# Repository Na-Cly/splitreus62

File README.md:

# splitreus62

Spacing on this is for choc keycaps only. MX sized keycaps will not work.

- [Atreus](https://github.com/technomancy/atreus) Phil Hagelberg
- [Atreus62](https://github.com/profet23/atreus62) Profet23

All these files were created from scratch, but out of respect for Phil I wanted to GPLv3 the project. 

Thanks to Phil for the staggering measurements from the atreus, and profet23 for the 62 key variant. 

This project uses MIT licensed KiCad footprints from Keebio and the Lily58 project.

### Features: 
- Reversible PCB supports MX/Alps/Choc Modified from keebio footprint.
- Pro Micro Footprint borrowed from the Lily58.
- supports SMD and through hole diodes.
- Breakout pins for led underglow.

### Known issues:
- SMD Diode footprint is only on the back-copper layer, so diodes have to be mounted on the bottom of the left half and the top of the right half.

## [Build Guide](/guide/README.MD)

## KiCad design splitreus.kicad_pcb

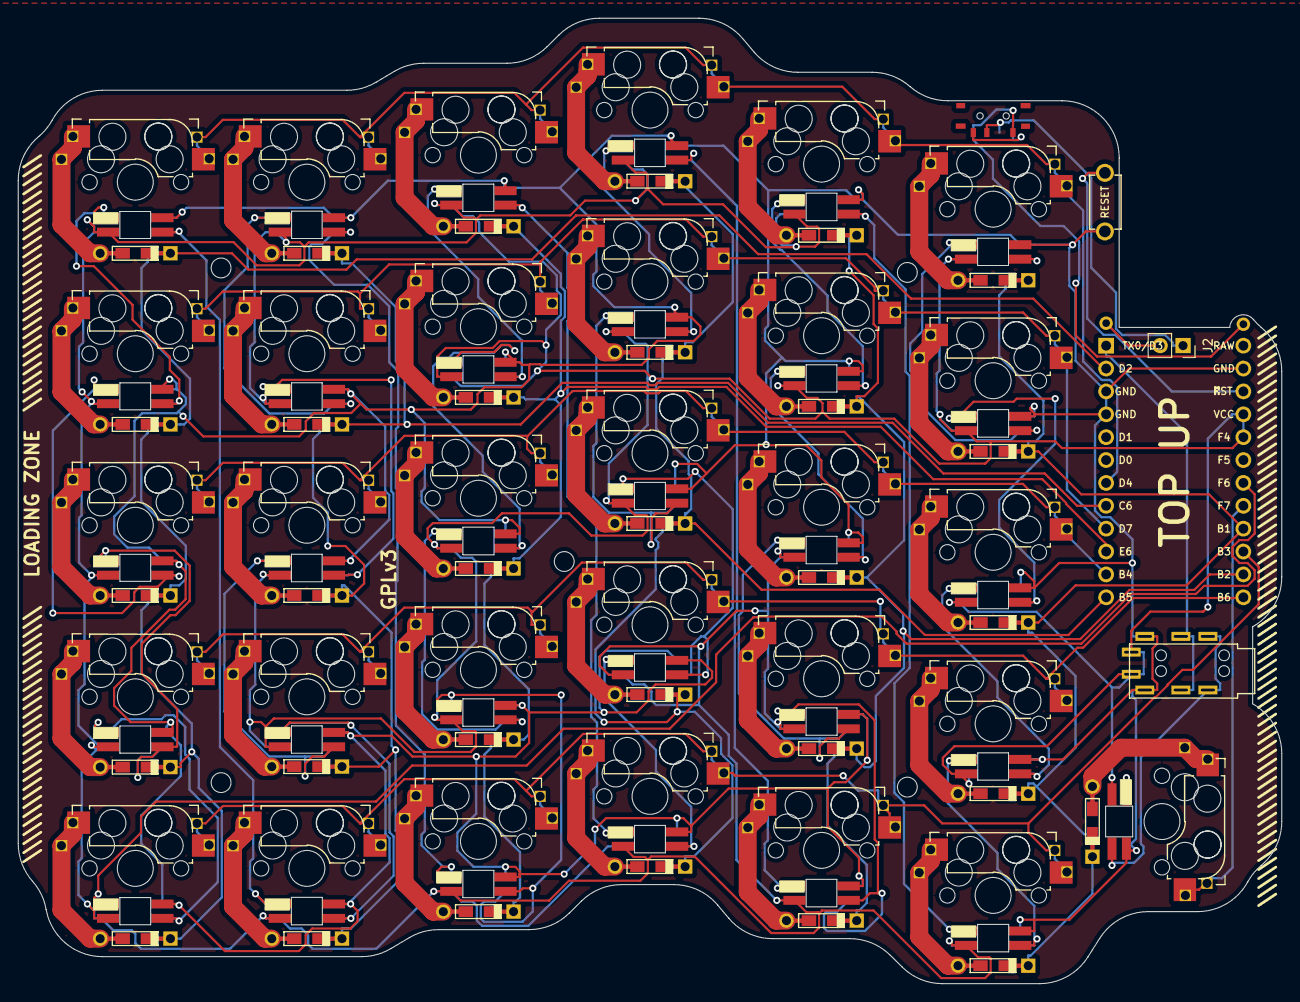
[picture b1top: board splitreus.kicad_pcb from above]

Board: 2 copper layers, 140.3 x 107.2 mm, 103 parts (1 on the bottom side), 81 nets.

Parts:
D0, D1, D2, D3, D4, D5, D6, D7, D8, D9, D10, D11, D12, D13, D14, D15, D16, D17, D18, D19, D20, D21, D22, D23, D24, D25, D26, D27, D28, D29, D30: 1N4148; Diode-Hybrid-reversible
D90, D91, D92, D93, D94, D95, D96, D97, D98, D99, D910, D911, D912, D913, D914, D915, D916, D917, D918, D919, D920, D921, D922, D923, D924, D925, D926, D927, D928, D929, D930: SK6812MINI; sk6812_minie_reversible
J1: TRRS; MJ-4PP-9
J2: battery; PinSocket_1x02_P2.54mm_Vertical
RST1: RST_SWITCH; TACT_SWITCH_TVBP06
SW0, SW1, SW2, SW3, SW4, SW5, SW6, SW7, SW8, SW9, SW10, SW11, SW12, SW13, SW14, SW15, SW16, SW17, SW18, SW19, SW20, SW21, SW22, SW23, SW24, SW25, SW26, SW27, SW28, SW29, SW30: SW_PUSH; Kailh_socket_MX_reversible_fix
SW91: SW_SPDT; reversible_power
U0: ProMicro; nice_nano
U1, U2, U3, U4, U5: HOLE; MountingHole_2.2mm_M2_DIN965

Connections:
B+: J2.1, SW91.2
B-: J2.2, U0.B-
COL0: D0.2, D1.2, D2.2, D3.2, D4.2, U0.2
COL1: D5.2, D6.2, D7.2, D8.2, D9.2, U0.8
COL2: D10.2, D11.2, D12.2, D13.2, D14.2, U0.10
COL3: D15.2, D16.2, D17.2, D18.2, D19.2, U0.12
COL4: D20.2, D21.2, D22.2, D23.2, D24.2, U0.14
COL5: D25.2, D26.2, D27.2, D28.2, D29.2, D30.2, U0.16
GND: D90.2, D91.2, D92.2, D93.2, D94.2, D95.2, D96.2, D97.2, D98.2, D99.2, D910.2, D911.2, D912.2, D913.2, D914.2, D915.2, D916.2, D917.2, D918.2, D919.2, D920.2, D921.2, D922.2, D923.2, D924.2, D925.2, D926.2, D927.2, D928.2, D929.2, D930.2, J1.3, RST1.2, U0.3, U0.4, U0.23
LED: D94.3, U0.18
unnamed: D0.1, SW0.1
unnamed: D1.1, SW1.1
unnamed: D2.1, SW2.1
unnamed: D3.1, SW3.1
unnamed: D4.1, SW4.1
unnamed: D5.1, SW5.1
unnamed: D6.1, SW6.1
unnamed: D7.1, SW7.1
unnamed: D8.1, SW8.1
unnamed: D9.1, SW9.1
unnamed: D10.1, SW10.1
unnamed: D11.1, SW11.1
unnamed: D12.1, SW12.1
unnamed: D13.1, SW13.1
unnamed: D14.1, SW14.1
unnamed: D15.1, SW15.1
unnamed: D16.1, SW16.1
unnamed: D17.1, SW17.1
unnamed: D18.1, SW18.1
unnamed: D19.1, SW19.1
unnamed: D20.1, SW20.1
unnamed: D21.1, SW21.1
unnamed: D22.1, SW22.1
unnamed: D23.1, SW23.1
unnamed: D24.1, SW24.1
unnamed: D25.1, SW25.1
unnamed: D26.1, SW26.1
unnamed: D27.1, SW27.1
unnamed: D28.1, SW28.1
unnamed: D29.1, SW29.1
unnamed: D30.1, SW30.1
unnamed: D90.1, D99.3
unnamed: D90.3, D91.1
unnamed: D91.3, D92.1
unnamed: D92.3, D93.1
unnamed: D93.3, D94.1
unnamed: D95.3, D96.1
unnamed: D96.3, D97.1
unnamed: D97.3, D98.1
unnamed: D98.3, D99.1
unnamed: D910.1, D919.3
unnamed: D910.3, D911.1
unnamed: D911.3, D912.1
unnamed: D912.3, D913.1
unnamed: D913.3, D914.1
unnamed: D95.1, D914.3
unnamed: D915.1, D924.3
unnamed: D915.3, D916.1
unnamed: D916.3, D917.1
unnamed: D917.3, D918.1
unnamed: D918.3, D919.1
unnamed: D920.1, D929.3
unnamed: D920.3, D921.1
unnamed: D921.3, D922.1
unnamed: D922.3, D923.1
unnamed: D923.3, D924.1
unnamed: D925.3, D926.1
unnamed: D926.3, D927.1
unnamed: D927.3, D928.1
unnamed: D928.3, D929.1
ROW0: SW0.2, SW5.2, SW10.2, SW15.2, SW20.2, SW25.2, U0.7
ROW1: SW1.2, SW6.2, SW11.2, SW16.2, SW21.2, SW26.2, U0.9
ROW2: SW2.2, SW7.2, SW12.2, SW17.2, SW22.2, SW27.2, U0.11
ROW3: SW3.2, SW8.2, SW13.2, SW18.2, SW23.2, SW28.2, U0.13
ROW4: SW4.2, SW9.2, SW14.2, SW19.2, SW24.2, SW29.2, U0.15
ROW5: SW30.2, U0.17
RST: RST1.1, U0.22
SERIAL: J1.2, U0.1
V+: SW91.1, U0.B+
VCC: D90.4, D91.4, D92.4, D93.4, D94.4, D95.4, D96.4, D97.4, D98.4, D99.4, D910.4, D911.4, D912.4, D913.4, D914.4, D915.4, D916.4, D917.4, D918.4, D919.4, D920.4, D921.4, D922.4, D923.4, D924.4, D925.4, D926.4, D927.4, D928.4, D929.4, D930.4, J1.4, U0.20, U0.21
to_right: D930.1, J1.1

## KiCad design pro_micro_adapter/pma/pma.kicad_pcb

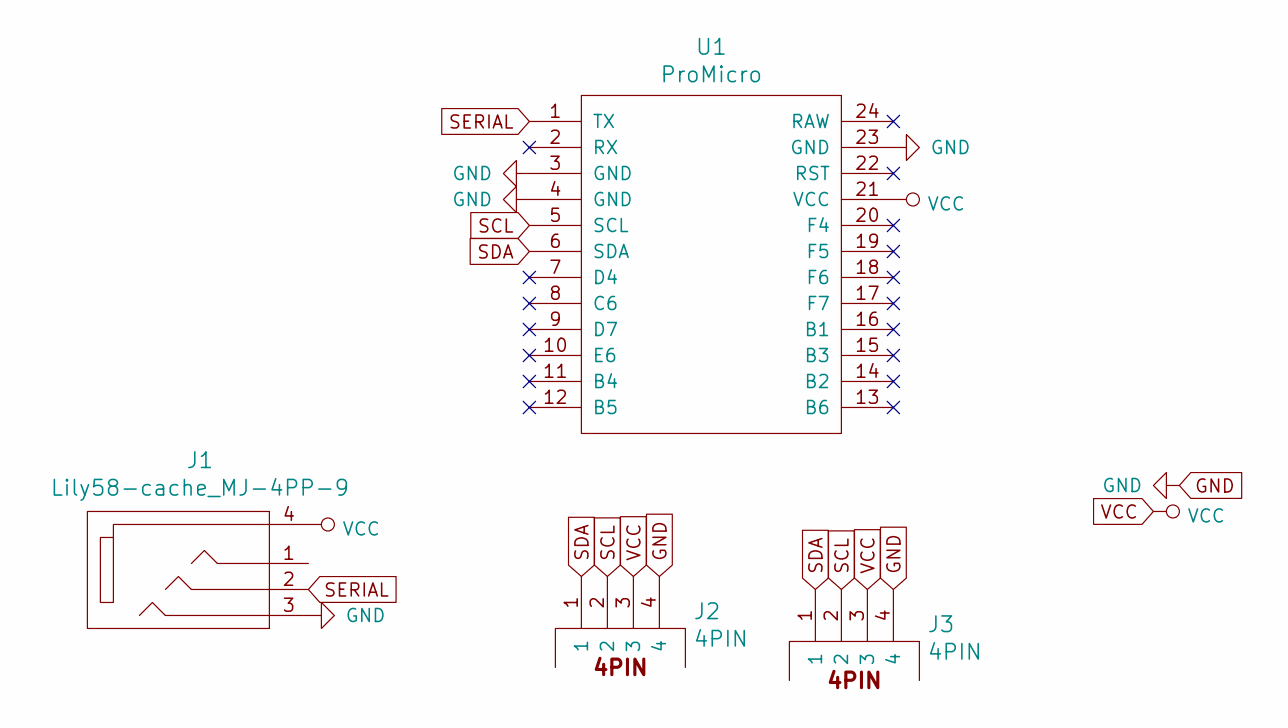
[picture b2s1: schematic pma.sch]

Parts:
J1: Lily58-cache_MJ-4PP-9; PJ-606-6A
J2, J3: 4PIN; PinHeader_1x04_P2.54mm_Vertical
U1: ProMicro; nice_nano

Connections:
GND: J1.3, J2.4, J3.4, U1.3 (GND), U1.4 (GND), U1.23 (GND)
SCL: J2.2, J3.2, U1.5 (SCL)
SDA: J2.1, J3.1, U1.6 (SDA)
SERIAL: J1.2, U1.1 (TX)
VCC: J1.4, J2.3, J3.3, U1.21 (VCC)

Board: 2 copper layers, 4 parts (0 on the bottom side), 5 nets, no tracks yet.

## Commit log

2020-03-10 Intial Commit
2020-04-08 Added Rev1.1
    Updated diode footprints, added rst silk screen to reset pins
2020-04-08 Created kailh_hot_swap
2020-04-11 Updated file
2020-04-11 updated from cm to mm
2020-04-11 updated files
2020-06-06 Changed some things
2020-06-09 Inital
2020-06-09 Cleanup
2020-06-28 Initial changes
2020-06-28 add usb
2020-06-29 updated schematic
2020-06-29 more updates
2020-07-03 Lots of changes
2020-07-05 Untested, unverified mid mount trrs
2020-07-05 Updated to 18.05x17.05
2020-07-05 traces
2020-07-05 18x17
2020-07-06 Updated again
2020-07-08 Final? probably not.
2020-07-11 updated radius
2020-11-11 dumb stuff
2021-03-06 hot swap choc
2021-03-06 semi done
2021-03-08 design updates
2021-03-13 a lot
2021-03-25 traces routed
2021-03-27 leds
2021-03-27 leds and placements
2021-03-31 holes and leds
2021-03-31 auto route leds
2021-04-02 fin?
2021-04-02 tracies
2021-06-06 upload
2021-06-10 change
2021-06-11 autoroute
2021-06-12 moved stuff
2021-06-25 Revert "updates"
    This reverts commit 91e359a53e5c4edd87a06c810b9b1645f14d0229.
2021-06-26 needs silk
2021-06-26 pro micro adapter
2021-06-26 silk
2021-06-26 final, ordered
2021-07-13 added edges for no bottom case
2021-09-20 changed stuff
2021-09-22 missing silk
2021-09-26 lots
2021-10-09 fix bottom case hole alignment
2022-03-18 Update fp-info-cache
